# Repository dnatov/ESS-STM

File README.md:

# ESS-STM
A GameCube/N64 ESS Adapter/Input Viewer for Ocarina of Time implemented on an STM32.

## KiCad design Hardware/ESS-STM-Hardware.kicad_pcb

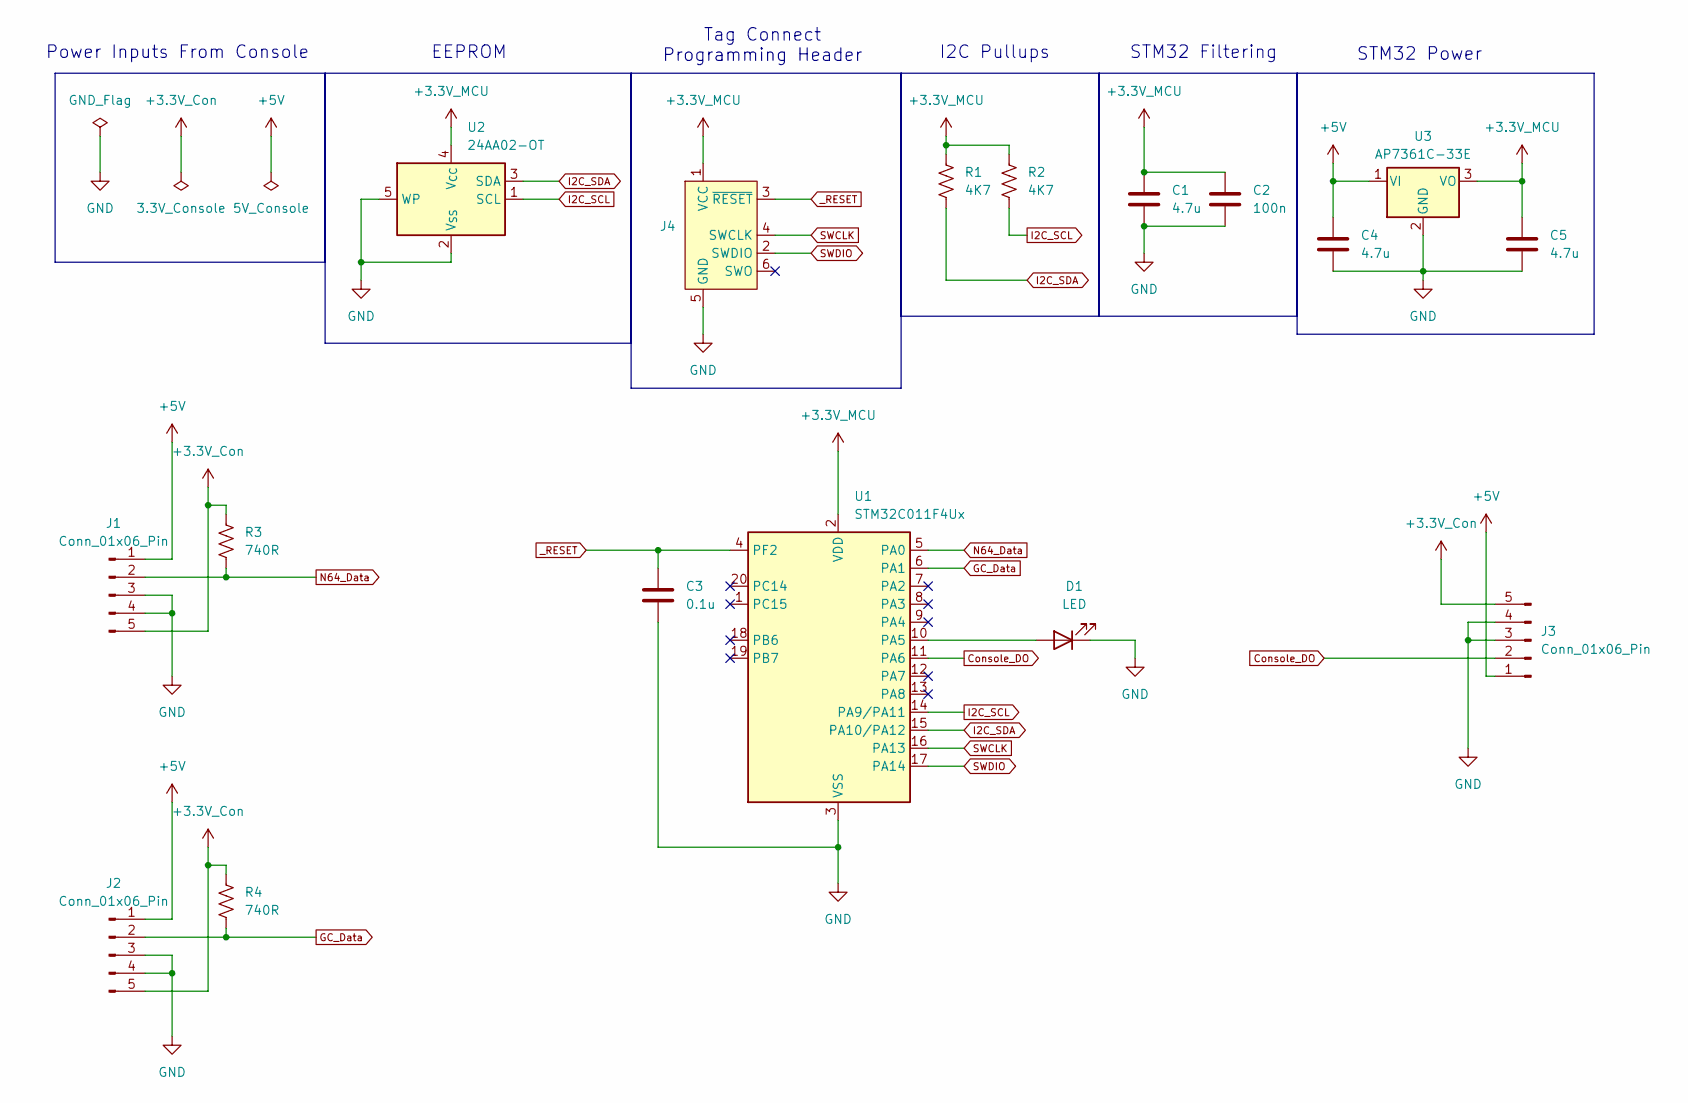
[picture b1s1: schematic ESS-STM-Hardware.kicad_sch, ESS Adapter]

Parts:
C1: 4.7u; D_0603_1608Metric
C2: 100n; C_0603_1608Metric
C3: 0.1u; C_0603_1608Metric
C4, C5: 4.7u; C_0603_1608Metric
D1: LED; LED_0805_2012Metric; Part Number KPT-2012LVVBC-D
J1, J2, J3: Conn_01x06_Pin; JST_PH_S5B-PH-SM4-TB_1x05-1MP_P2.00mm_Horizontal
J4: Conn_ARM_SWD_TagConnect_TC2030; Tag-Connect_TC2030-IDC-FP_2x03_P1.27mm_Vertical
R1, R2: 4K7; C_0603_1608Metric
R3, R4: 740R; C_0603_1608Metric
U1: STM32C011F4Ux; ST_UFQFPN-20_3x3mm_P0.5mm
U2: 24AA02-OT; SOT-23-5
U3: AP7361C-33E; SOT-223-3_TabPin2

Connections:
+3.3V_Con: J1.5, J2.5, J3.5, R3.1, R4.1
+3.3V_MCU: C1.1, C2.1, C5.1, J4.1 (VCC), R1.1, R2.1, U1.2 (VDD), U2.4 (V_{CC}), U3.3 (VO)
+5V: C4.1, J1.1, J2.1, J3.1, U3.1 (VI)
Console_DO: J3.2, U1.11 (PA6)
GC_Data: J2.2, R4.2, U1.6 (PA1)
GND: C1.2, C2.2, C3.2, C4.2, C5.2, D1.1 (K), J1.3, J1.4, J2.3, J2.4, J3.3, J3.4, J4.5 (GND), U1.3 (VSS), U2.2 (V_{SS}), U2.5 (WP), U3.2 (GND)
I2C_SCL: R2.2, U1.14 (PA9/PA11), U2.1 (SCL)
I2C_SDA: R1.2, U1.15 (PA10/PA12), U2.3 (SDA)
N64_Data: J1.2, R3.2, U1.5 (PA0)
unnamed: D1.2 (A), U1.10 (PA5)
SWCLK: J4.4 (SWCLK), U1.16 (PA13)
SWDIO: J4.2 (SWDIO), U1.17 (PA14)
_RESET: C3.1, J4.3 (~RESET), U1.4 (PF2)

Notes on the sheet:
EEPROM
Tag Connect Programming Header
STM32 Power
STM32 Filtering
I2C Pullups
Power Inputs From Console

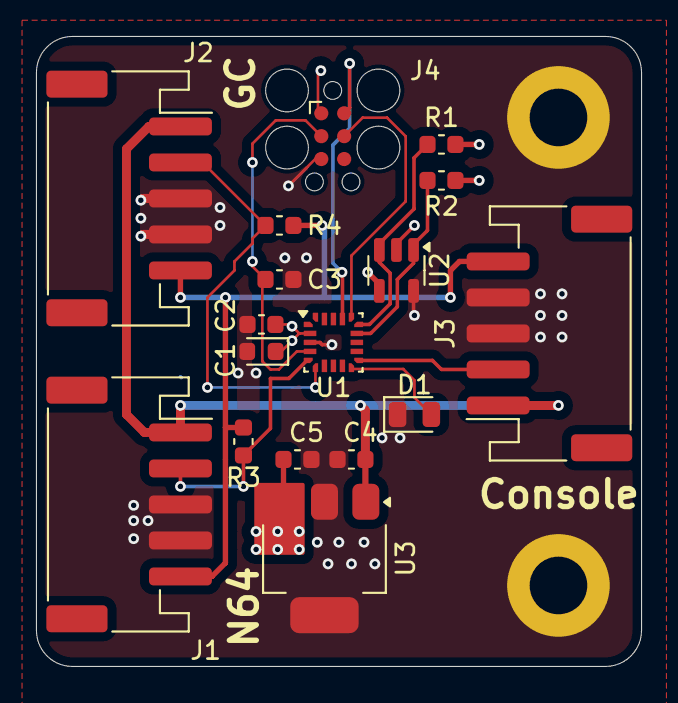
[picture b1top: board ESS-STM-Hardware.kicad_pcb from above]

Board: 4 copper layers, 33.6 x 35.0 mm, 17 parts (0 on the bottom side), 13 nets.

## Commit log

2024-10-29 Adding initial KiCAD schematic design with STM32C011
2024-11-05 Finished Schematic
2025-01-15 Some changes to board design
2025-01-19 Finish PCB Rev 0 Design
